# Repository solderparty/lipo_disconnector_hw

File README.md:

# LiPo Disconnector

This little board allows you to get inbetween a LiPo battery and a board/device that requires the battery. This way you can easily disconnect the LiPo from the device without having to remove the JST PH connector over and over, all you have to do is remove the jumper! You can also use the header on the Disconnector as a current-measuring point.

NOTE: Before connecting the battery, always make sure the polarity is correct.

# Links

For more information visit https://lipo-disconnector.solder.party/

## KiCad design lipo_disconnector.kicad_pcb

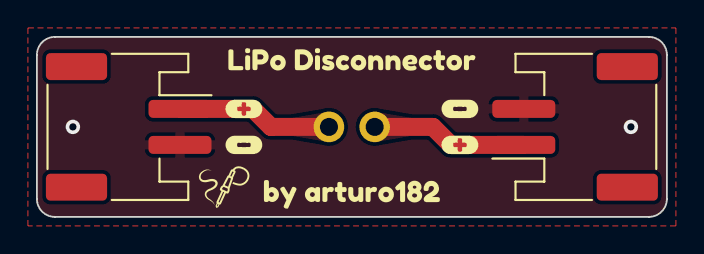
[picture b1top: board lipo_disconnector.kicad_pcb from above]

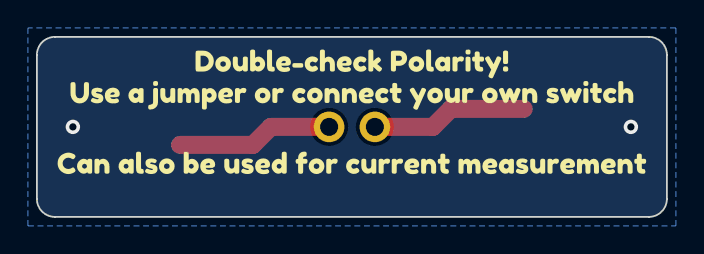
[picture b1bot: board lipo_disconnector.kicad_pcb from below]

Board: 2 copper layers, 35.0 x 10.0 mm, 12 parts (3 on the bottom side), 3 nets.

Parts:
J1: Conn_Batt1; JST_PH_S2B-PH-SM4-TB_1x02-1MP_P2.00mm_Horizontal
J2: Conn_Batt2; JST_PH_S2B-PH-SM4-TB_1x02-1MP_P2.00mm_Horizontal
J3: Conn_Jumper; PinHeader_1x02_P2.54mm_Vertical
kibuzzard-62E1C2B7, kibuzzard-62E1C2B7#2, kibuzzard-62E1C2B7#3, kibuzzard-62E1C2B7#4: G***; kibuzzard-62E1C2B7
kibuzzard-62E1C3A6: G***; kibuzzard-62E1C3A6
kibuzzard-62E1C4AB: G***; kibuzzard-62E1C4AB
kibuzzard-62E2BF3F: G***; kibuzzard-62E2BF3F
kibuzzard-62E2BF4D: G***; kibuzzard-62E2BF4D
kibuzzard-62E2BF27: G***; kibuzzard-62E2BF27

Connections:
GND: J1.2, J2.2
unnamed: J1.1, J3.1
unnamed: J2.1, J3.2

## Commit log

2022-09-12 Initial import
